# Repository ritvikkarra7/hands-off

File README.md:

# hands-off
EE 327 Theremin Project

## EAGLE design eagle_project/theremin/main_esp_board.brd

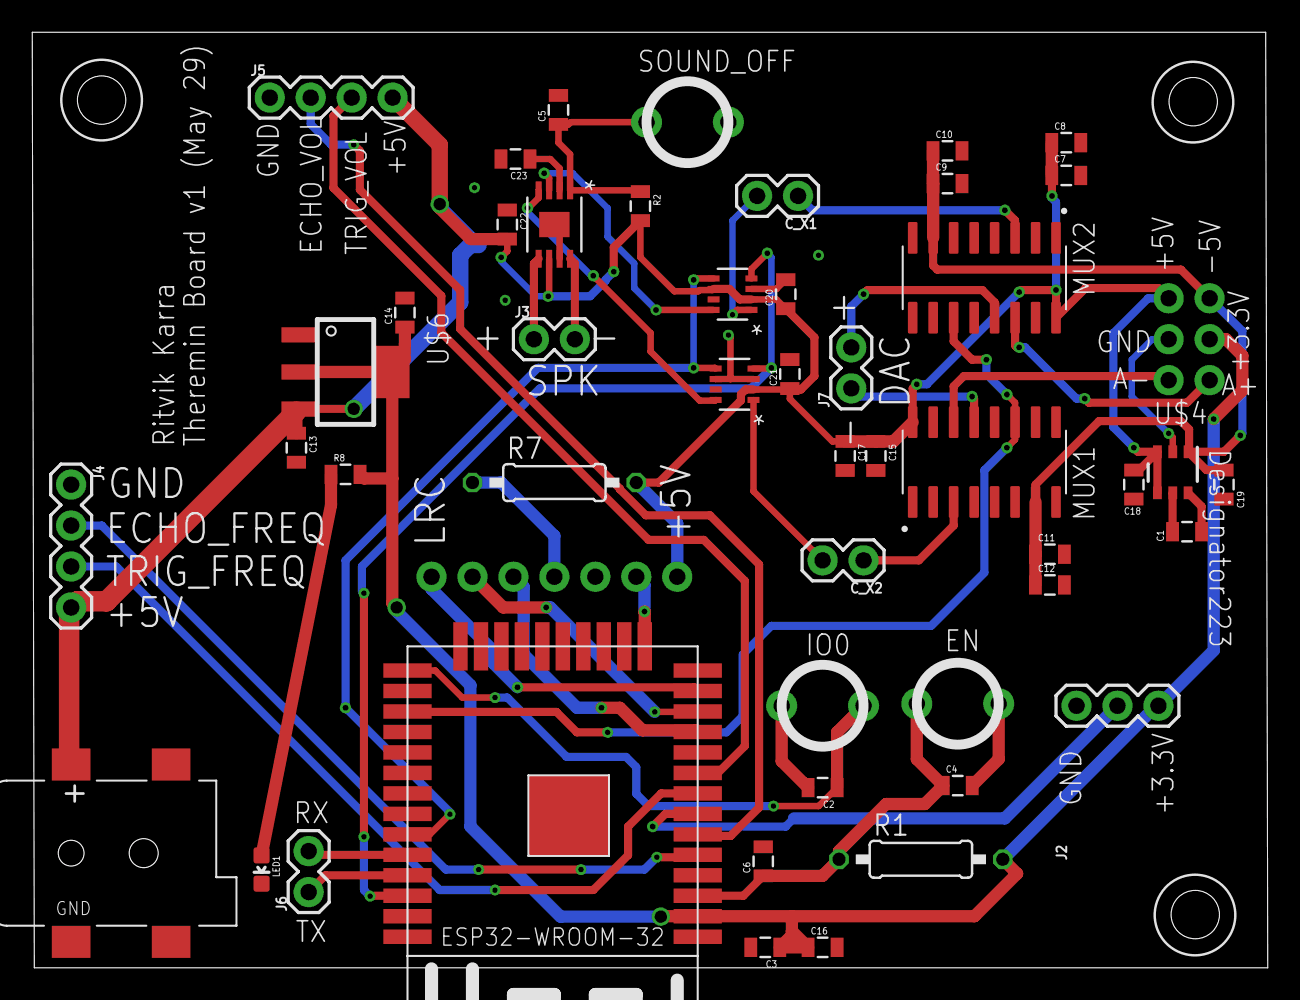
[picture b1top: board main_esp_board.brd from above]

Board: 2 copper layers, 76.6 x 58.0 mm, 50 parts (1 on the bottom side), 37 nets.

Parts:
AMPLIFIER: TPA6211A1TDGNRQ1DGN8_1P89X1P57-L; DGN8_1P89X1P57-L
C1: 1 uF; 0805
C2, C4, C5, C6, C7, C9, C11, C15, C16, C20, C21: 0.1uF; 0805
C3: 22uF; 0805
C8, C10, C12, C13, C14, C17, C22: 1uF; 0805
C18, C19: 2.2 uF; 0805
C23: 0.22uF; 0805
C_X1, C_X2: 0.16uF; 1X02
DIGIPOT1, DIGIPOT2: CAT5171TBI-50GT3SOT23-8_ONS-L; SOT23-8_ONS-L
EN: SWITCH_BTN_NO; BTN_2
ESP32: ESP32-WROOM
IO0: SWITCH_BTN_NO; BTN_2
J1: 1X07
J2: 455-1750-1-ND; 1X03
J3: SPEAKER; 1X02
J4, J5: 1X04
J6, J7: 1X02
LED1: BLUE; LED-0603
MUX1, MUX2: CD4051BM96; SOIC127P600X175-16N
R1, R7: 0207/10
R2: 0805
R8: 330R; 0805
REGULATOR: LM2776DBVRDBV0006A_L; DBV0006A_L
SOUND_OFF: SWITCH_BTN_NO; BTN_2
U$4: 2X3_PROG; 2X3_0.1IN
U$5: BARREL_2.1MMSMT; DCJACK_2MM_SMT
U$6: VREG-3V3; R-PDSO-G4_TI

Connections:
-VDD5V0: C9.1, C10.1, C11.1, C12.1, C19.1, MUX1.7, MUX2.7, REGULATOR.1, U$4.2
AMPLIFIER_+: C_X1.1, MUX2.3
AMPLIFIER_-: C_X2.1, MUX1.3
ANALOG+: MUX2.14, U$4.6
ANALOG-: MUX1.14, U$4.5
BCLK: ESP32.IO27, J1.2
DAC+: J7.2, MUX2.13
DAC-: J7.1, MUX1.13
DIN: ESP32.IO26, J1.3
ECHO_FREQ: ESP32.SENSOR_VN, J4.2
ECHO_VOL: ESP32.IO34, J5.2
EN: C4.1, C6.1, EN.P$1, ESP32.EN, R1.1
GAIN: J1.4, R7.1
GND: AMPLIFIER.7, AMPLIFIER.EPAD, C2.2, C3.2, C4.2, C5.2, C6.2, C7.2, C8.2, C9.2, C10.2, C11.2, C12.2, C13.2, C14.2, C15.2, C16.2, C17.2, C18.2, C19.2, C20.2, C21.2, C22.1, C23.2, DIGIPOT1.3, DIGIPOT1.6, DIGIPOT2.3, EN.P$2, ESP32.GND1, ESP32.GND2, ESP32.GND3, ESP32.GND4, ESP32.GND5, IO0.P$2, J1.6, J2.1, J4.1, J5.1, LED1.C, MUX1.6, MUX1.8, MUX1.9, MUX1.10, MUX2.6, MUX2.8, MUX2.9, MUX2.10, REGULATOR.2, SOUND_OFF.P$2, U$4.3, U$5.GND, U$5.GNDBREAK, U$6.1
IN+: AMPLIFIER.3, DIGIPOT2.8
IN-: AMPLIFIER.4, DIGIPOT1.8
IO0: C2.1, ESP32.IO0, IO0.P$1
LRC: ESP32.IO14, J1.1
unnamed: C1.1, REGULATOR.5
unnamed: C1.2, REGULATOR.6
unnamed: AMPLIFIER.2, C23.1
unnamed: C_X1.2, DIGIPOT2.1
unnamed: C_X2.2, DIGIPOT1.1
unnamed: LED1.A, R8.1
POT_IN: ESP32.IO35, J2.2
RX: ESP32.RX, J6.2
SCL: DIGIPOT1.4, DIGIPOT2.4, ESP32.IO22
SDA: DIGIPOT1.5, DIGIPOT2.5, ESP32.IO21
SD_AMP: AMPLIFIER.1, C5.1, R2.1, SOUND_OFF.P$1
SEL: ESP32.IO16, MUX1.11, MUX2.11
SPK+: AMPLIFIER.5, J3.1
SPK-: AMPLIFIER.8, J3.2
TRIG_FREQ: ESP32.IO32, J4.3
TRIG_VOL: ESP32.IO33, J5.3
TX: ESP32.TX, J6.1
VDD3V3: C3.1, C14.1, C16.1, ESP32.3V3, J2.3, R1.2, R8.2, U$4.4, U$6.2, U$6.4
VDD5V0: AMPLIFIER.6, C7.1, C8.1, C13.1, C15.1, C17.1, C18.1, C20.1, C21.1, C22.2, DIGIPOT1.2, DIGIPOT2.2, DIGIPOT2.6, J1.7, J4.4, J5.4, MUX1.16, MUX2.16, R2.2, R7.2, REGULATOR.3, REGULATOR.4, U$4.1, U$5.PWR1, U$6.3

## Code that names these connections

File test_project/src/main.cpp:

#include <Arduino.h>
#include <SPIFFS.h>
#include "WaveFormGenerator.h"
#include "I2SOutput.h"
#include "Server.h"
#include "UltrasonicSensor.h"
#include "CAT5171.h"
#include "utilities.h"

// TODO: 
// 1) Handle mode switching from website
// 2) Add the use of scales from website to select a scale to play in 

// i2s pins
i2s_pin_config_t i2sPins = {
    .bck_io_num = GPIO_NUM_27,
    .ws_io_num = GPIO_NUM_14,
    .data_out_num = GPIO_NUM_26,
    .data_in_num = -1};

I2SOutput *output;
WaveFormGenerator *sampleSource;

#define trig_freq GPIO_NUM_32
#define trig_vol GPIO_NUM_33
#define echo_freq GPIO_NUM_39
#define echo_vol GPIO_NUM_34
#define pot GPIO_NUM_35

TaskHandle_t frequencyTaskHandle = NULL;
TaskHandle_t potTaskHandle = NULL;
TaskHandle_t volumeTaskHandle = NULL;
CAT5171 digipot; // Digital Potentiometer for volume control

UltrasonicSensor freqSensor(trig_freq, echo_freq, 1.0, 100.0);
UltrasonicSensor volSensor(trig_vol, echo_vol, 1.0, 100.0);

double magnitude = 0.05; 

// Function to calculate distance using ultrasonic sensor
void frequencyTask(void *params) {
  while (true) {
    float duration = freqSensor.readDuration();
    float frequency = sampleSource->getNoteFromDuration(duration);

    if (frequency < 20 || isnan(frequency)) {
      sampleSource->setFrequency(0);
      sampleSource->setMagnitude(0);
      broadcastFrequency(0);
    } else {
      sampleSource->setFrequency(frequency);
      sampleSource->setMagnitude(magnitude);
      broadcastFrequency(frequency);
    }

    vTaskDelay(20 / portTICK_PERIOD_MS);
  }
}

void potTask(void *params) {
  while (true) {

    Serial.println("Potentiometer Task Running");
    if (digitalRead(SEL) == HIGH){

      int potValue = analogRead(pot);
      byte gain = map(potValue, 0, 4095, 0, 255);
      Serial.println("Potentiometer Value: " + String(potValue) + ", Gain: " + String(gain));
      digipot.setWiperBoth(gain); 
    }

    vTaskDelay(20 / portTICK_PERIOD_MS);

  }
}

void volumeTask(void *params) {
  while (true) {

    Serial.println("Volume Task Running");
    if (digitalRead(SEL) == LOW) {

      float duration = volSensor.readDuration();
      magnitude = 0.3 * exp(-0.00285 * duration); 
      Serial.println("Volume Duration: " + String(duration) + " ms, Magnitude: " + String(magnitude));
      if (magnitude > 0.3 || magnitude < 0.0001) {
        sampleSource->setMagnitude(0); // Cap volume at 0.3
      } 
      sampleSource->setMagnitude(magnitude); // Set magnitude based on volume

    }

    vTaskDelay(20 / portTICK_PERIOD_MS);

  }
}

void setup() {
  Serial.begin(115200);
  Serial.println("Starting up");

  freqSensor.begin();
  volSensor.begin();
  digipot.setWiperBoth(200); // Initialize digital potentiometer to 0

  SPIFFS.begin();

  startWebServices();

  pinMode(SEL, OUTPUT); // GPIO for the multiplexer control
  digitalWrite(SEL, LOW); // mux is low for digital mode by default
  sampleSource = new WaveFormGenerator(40000, 2000, 0.05);

  Serial.println("Starting I2S Output");
  output = new I2SOutput();
  output->start(I2S_NUM_1, i2sPins, sampleSource);

  // Create a task to handle frequency updates
  xTaskCreate(
    frequencyTask,
    "FrequencyTask",
    4096,
    NULL,
    2,
    &frequencyTaskHandle
  );

  xTaskCreate(
    potTask, 
    "PotentiometerTask",
    4096, 
    NULL, 
    2, 
    &potTaskHandle
  ); 

  xTaskCreate(
    volumeTask, 
    "VolumeTask",
    8192, 
    NULL, 
    2, 
    &volumeTaskHandle
  );

  vTaskDelete(NULL);
}

void loop() {
  // Empty loop as all tasks are handled by FreeRTOS
}

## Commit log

2025-04-17 hartley osc
2025-04-18 oscillator + start of mixer
2025-04-27 fixed oscillator + mixer
2025-05-02 theremin code
2025-05-02 sin wave generator renamed
2025-05-02 oops missed a rename
2025-05-02 code can handle multiple waveforms
2025-05-02 improved frequency sensitivity of theremin
2025-05-03 website+ltspice
2025-05-06 debugged: fixed coupled ultrasonic sensors
2025-05-06 use js file instead of in-file scripting
2025-05-06 website directory moved down a level
2025-05-07 added website code
2025-05-08 fix: website + code interactivity by serving setWaveform endpoint
2025-05-08 website interface finally works! i hate javascript
2025-05-11 esp32 changed to client
2025-05-11 use RTOS
2025-05-11 web serial monitor
2025-05-11 streaming frequencies onto website
2025-05-12 include newping library
2025-05-12 added TODO
2025-05-13 fix: cutoff output when hand is away
2025-05-13 Kalman filter for ultrasonic sensor
2025-05-14 eagle
2025-05-15 updated main board
2025-05-15 update gitignore
2025-05-15 mode switching UI complete
2025-05-25 updated board
2025-05-26 update website
2025-05-26 added scales to website
2025-05-29 digipot code + schematic
2025-05-29 added I2C connections
2025-05-29 added board files
2025-06-07 idk a bunch of code
2025-06-10 project complete

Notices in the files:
parts and their libraries:
SparkFun-Connectors: Licensing: Creative Commons ShareAlike 4.0 International - https://creativecommons.org/licenses/by-sa/4.0
COPYRIGHT: Copyright (C) 2025 Ultra Librarian. All rights reserved.
